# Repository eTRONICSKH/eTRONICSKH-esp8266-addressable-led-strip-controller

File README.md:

# esp-addressable-led-strip-controller
## Objective

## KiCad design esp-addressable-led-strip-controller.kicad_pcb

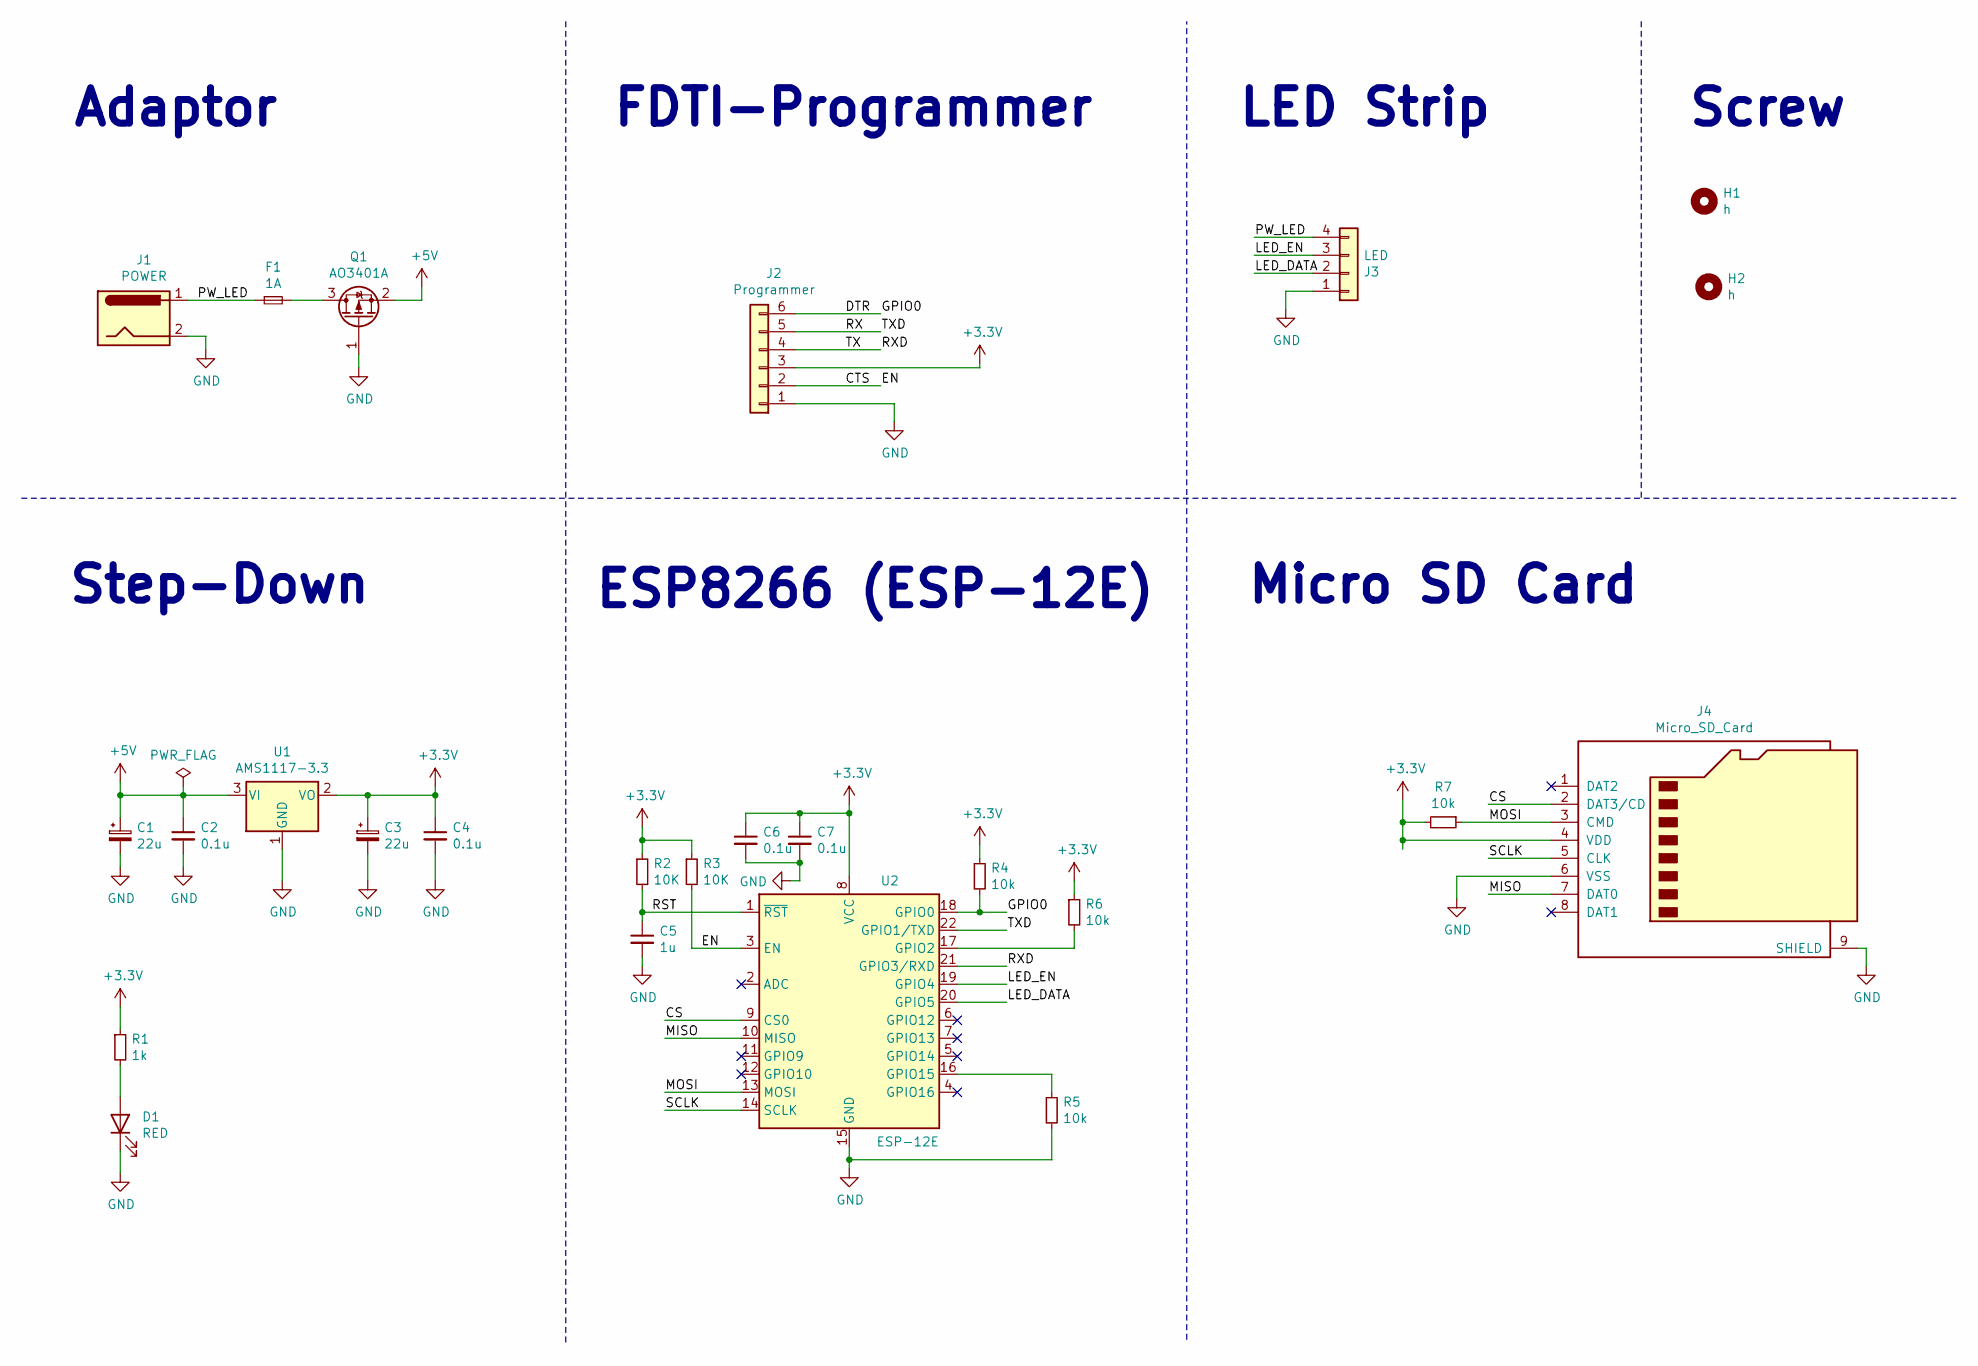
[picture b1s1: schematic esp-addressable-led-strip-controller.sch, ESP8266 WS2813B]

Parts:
C1, C3: 22u; CP_EIA-3216-18_Kemet-A
C2, C4, C6, C7: 0.1u; C_0603_1608Metric
C5: 1u; C_0805_2012Metric
D1: RED; LED_0805_2012Metric
F1: 1A; Fuse_1812_4532Metric
H1, H2: h; MountingHole_2.2mm_M2_DIN965_Pad
J1: POWER; BarrelJack_CLIFF_FC681465S_SMT_Horizontal
J2: Programmer; Harwin_M20-89006xx_1x06_P2.54mm_Horizontal
J3: LED; JST_VH_B4PS-VH_1x04_P3.96mm_Horizontal
J4: Micro_SD_Card; SUNTECH_ST-TF-003A
Q1: AO3401A; SOT-23
R1: 1k; R_0603_1608Metric
R2, R3: 10K; R_0603_1608Metric
R4, R5, R6, R7: 10k; R_0603_1608Metric
U1: AMS1117-3.3; SOT-223-3_TabPin2
U2: ESP-12E

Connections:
+3V3: C3.1, C4.1, C6.1, C7.1, J2.3, J4.4 (VDD), R1.1, R2.1, R3.1, R4.1, R6.1, R7.2, U1.2 (VO), U2.8 (VCC)
+5V: C1.1, C2.1, Q1.2 (S), U1.3 (VI)
/CS: J4.2 (DAT3/CD), U2.9 (CS0)
/CTS: J2.2, R3.2, U2.3 (EN)
/DTR: J2.6, R4.2, U2.18 (GPIO0)
/LED_DATA: J3.2, U2.20 (GPIO5)
/LED_EN: J3.3, U2.19 (GPIO4)
/MISO: J4.7 (DAT0), U2.10 (MISO)
/MOSI: J4.3 (CMD), R7.1, U2.13 (MOSI)
/PW_LED: F1.1, J1.1, J3.4
/RST: C5.1, R2.2, U2.1 (~RST)
/RX: J2.5, U2.22 (GPIO1/TXD)
/RXD: J2.4, U2.21 (GPIO3/RXD)
/SCLK: J4.5 (CLK), U2.14 (SCLK)
GND: C1.2, C2.2, C3.2, C4.2, C5.2, C6.2, C7.2, D1.1 (K), J1.2, J2.1, J3.1, J4.6 (VSS), J4.9 (SHIELD), Q1.1 (G), R5.2, U1.1 (GND), U2.15 (GND)
unnamed: D1.2 (A), R1.2
unnamed: F1.2, Q1.3 (D)
unnamed: R5.1, U2.16 (GPIO15)
unnamed: R6.2, U2.17 (GPIO2)

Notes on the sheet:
Adaptor
Step-Down
FDTI-Programmer
ESP8266 (ESP-12E)
Micro SD Card
LED Strip
Screw

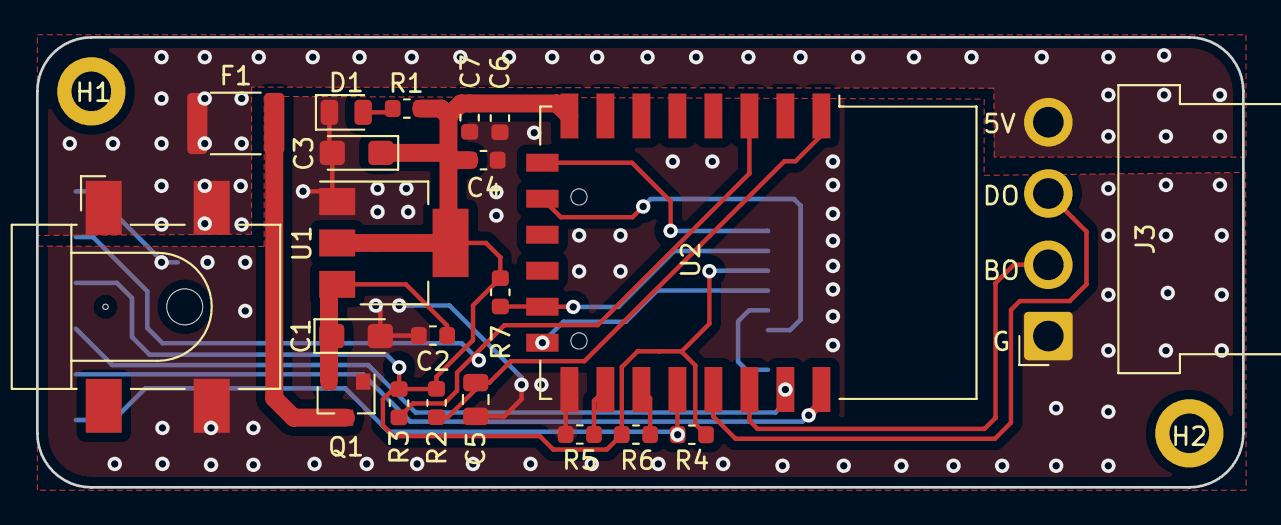
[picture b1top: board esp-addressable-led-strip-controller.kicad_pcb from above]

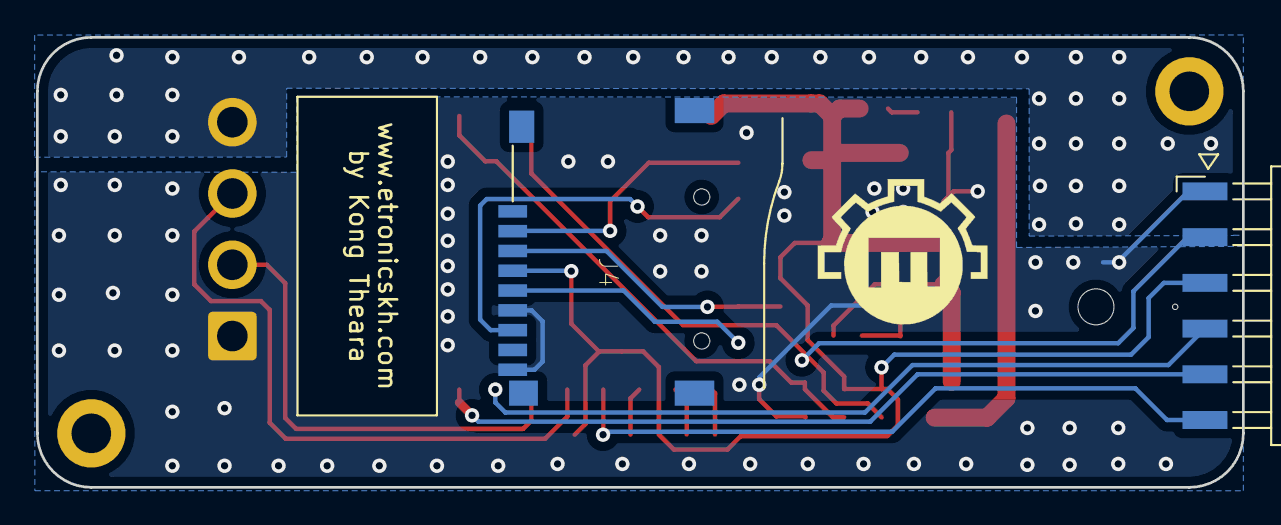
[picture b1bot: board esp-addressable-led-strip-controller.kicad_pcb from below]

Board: 2 copper layers, 67.0 x 25.0 mm, 25 parts (2 on the bottom side), 19 nets.

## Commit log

2021-02-07 add files
2021-02-07 edit readme
